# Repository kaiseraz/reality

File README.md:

# Reality: the AI workspace that morphs to the task

**Reality is an open-source AI workspace that turns one sentence into a checked result: a team of AI bots, each with its own Linux computer, builds the work, and independent code verifies every number before it is shown.**

**Built during the Meta Global AI Developer Hackathon (November 2026) on Meta's Muse Spark.** Licensed under Apache 2.0.

You bring only the task. Reality brings the rest: it **acquires the capabilities** the task needs at runtime (a statistics library, a SQL engine, a chemistry toolkit, a CAD kernel), **shapes its workspace** around the work (data, lab, 3D CAD, a bot's live computer), and puts a **team of bots** on it, each with its own Linux computer. What makes it different: **every result is checked by code, independently**. No bot, not even the lead, can declare its own work done.

Built for the Meta Global AI Developer Hackathon, on Meta's Muse Spark.

- Submission text: [docs/submission.md](docs/submission.md)
- Plan and architecture: [docs/execution-plan.md](docs/execution-plan.md) · Decisions: [docs/adr/](docs/adr/)
- Evaluation: [docs/eval/report.md](docs/eval/report.md)

## What it does

**One lead, a team it hires.** Everyone starts with one bot, the lead "Reality". Ask it something small and it answers. Give it a real job and it proposes a team on a card: specialists with a mission, a deliverable, a budget, the web domains and setup their computers need, and how code will check the job. You hire the team once. Each specialist then works under a **contract**: it hands in its work, and code decides whether it is met (a command on its computer exits 0, a file exists with the right content, a Reality task passes verification, or you accept it). Late or unproven work fails. Released bots rest with their **record** of met and failed contracts, and the lead hires proven ones again. Bots save scripts that worked as **team skills** for others to reuse.

**Every bot has its own computer.** A persistent Linux machine per bot (the open-source [AIO Sandbox](https://github.com/agent-infra/sandbox), Apache 2.0) with a browser, a terminal and a home folder that survives restarts. Bots run commands, write files and browse; you watch all computers live as tiles on the right and click one to watch it large or take control. The computers sit on a Docker network **without internet**; Reality's gateway lets each one reach only the domains you allowed, only public addresses on ports 80/443, and logs every decision. Blocked domains turn into Allow/Deny cards.

**A real folder on your computer.** The bots in a chat share one project folder inside the sandbox, and Reality copies what they make to a folder of yours (by default under Reality in your documents; choose another in the Files tab). No bot computer ever has your folder mounted. A file you changed is not overwritten, the new version lands beside it, and nothing there is deleted. On a server, set `PROJECT_FOLDERS=off`.

**More than a computer.** When a picture says it better than words, a bot draws it with `show_visual`: a diagram, a plan or a small interactive page opens beside the chat and updates in versions. It runs in a closed frame without access to Reality's data or the network, and is marked as drawn, not checked.

**It acquires what it lacks.** When a task needs something the sandbox does not have, Reality finds a candidate (a PyPI wheel, or an MCP server from PyPI, npm or the MCP registry), inspects it without running it (files, licence, OSV advisories), asks you once, installs it into an isolated layer, runs a requirement test, then uses and reuses it. Shown live: statsmodels (seasonality), DuckDB via MCP (SQL), RDKit (molecules), OpenCascade (CAD).

**Lab and engineering.** Simulations for thin films, ring resonators, tolerance stacks, quantum circuits, molecules and crystals, each re-checked by an independent method. Ask for a jet engine and Reality acquires a CAD kernel and builds a **turbofan of about 2,000 named solids**, exports **STEP** for any CAD program and shows it in 3D: orbit, cut it open, hide groups, search the parts list. An independent check recounts the parts and recomputes volumes from the meshes. No Fusion, no Python on your machine.

**Design you can watch.** The lab also designs **circuit boards** (placement, a two-layer router with vias and 45° tracks, KiCad 8 board files, Gerber and drill files, part models) and **rockets and assemblies by hierarchy**, each re-checked by an independent method (the board by recomputing clearances and connectivity from the file itself). A bot's result then **opens in the real program on its own desktop**: a board in KiCad first as placed with the ratsnest, then routed, then in KiCad's 3D viewer with the part models; a jet engine in FreeCAD, about 1,900 parts built one at a time in under a minute, coloured by group, shell last and see-through. The web view shows the same boards in physically based 3D, with a build you can replay.

**Bots that operate the programs themselves.** A bot looks at its screen (a picture, plus the text on it read with OCR and its exact position) and uses mouse and keyboard, one action at a time: Muse Spark has opened KiCad's Inspect menu, run the Design Rules Checker, read the result, closed it and saved the board with its own keystrokes. Someone who changes a board by hand (the bot, or you after taking over its desktop) asks for `recheck_board`: the file as KiCad saved it goes through the same independent check, including whether any pad moved to another net.

**Data analysis with proof.** Reality plans, you approve, it runs in a locked-down sandbox, and every number is re-computed independently before it is shown as verified. Numbers a bot writes that no tool produced are flagged in the chat. Evaluation: 14 tasks (6 synthetic with known truth, 8 on NOAA Mauna Loa CO₂ and UCI Bike Sharing): **14/14 correct, 0 policy violations**; a fixed-tool baseline gets 7/14.

**Missions overnight.** Give a team a goal, criteria and a budget; it works until done. The verdict comes from code over fully verified evidence, with a report page.

**And:** research with citations checked against the source (OpenAlex, your notes), versioned pages, routines on a schedule, projects with dependencies and budgets, accounts.

**The interface.** A dark, calm workspace: the sidebar folds with Ctrl+B, the chat in the middle, the bots' computers on the right. Each bot is a [blobatar](https://blobatar.dev/) made from its name, so the same name is the same creature everywhere, and its face shows what it is doing (thinking, searching, working, waiting for you, done). The lead wears the interface's own white; a bot that joins a chat splits off it at the top of that chat, the way the two dots in the logo pull apart.

## Meta Muse Spark

Reality talks to Muse Spark through Meta's Anthropic-compatible Model API. It drives the **bots' conversations and tool use**, the **planner** (structured output via a forced tool call) and **research answers**. `PLANNER=auto` picks Meta whenever `META_MODEL_API_KEY` is set, then Claude, then built-in rules. Without any key, Reality still runs fully with deterministic planners.

Check a key in seconds:

```bash
npm run check:model
```

It verifies that the model answers, calls a tool and uses its result, gives structured output, and accepts all of Reality's bot tools, and says what to fix when a step fails. The bot model tolerates small endpoint differences (string tool arguments, odd stop reasons) and retries passing failures.

## Trust model

- **Verification by code.** Results, contracts and missions are judged by independent checks; a bot's own claim counts for nothing.
- **Sandboxes.** Analysis code runs in containers without network, read-only, non-root. Capabilities are mounted read-only after inspection and your approval.
- **Bot computers.** Isolated network, allowlisted egress through a gateway, no host mounts, resource limits, idle shutdown, a full log. Their screens reach your browser only through Reality, so the computer's key never does.
- **You decide.** Installations, plans with custom code, hiring a team and web access are approvals; a deterministic policy auto-approves only fully machine-checked plans that use reviewed analyses.
- **Tool servers.** Every server a bot gets runs in a sandbox with no network, unless you approved domains for it; then the gateway is its only way out and every other host is refused and named. A hosted server is reached over https only, and its card says who receives what a bot sends.
- **Skills from GitHub, when you ask.** Written methods a bot can get, pinned to a commit, read as text, checked for licence and hidden instructions, and usable once you approved what they say. They bring no rights: their scripts run only on the bot's own computer.
- **Secrets.** Reality's own keys stay in the server and never enter sandboxes or computers. A key you type on a tool server's approval card is stored encrypted, goes only to that server, works only for your bots, and is cut out of whatever comes back. No API returns it and bots never see it.

## Quick start

On Windows, double-click `Start.bat`: it checks Node and Docker, starts Docker Desktop if needed, installs and builds what is missing on the first run (the bot computers are a one-time download of about 9 GB), starts Reality and opens http://localhost:5173.

Or by hand:

```bash
npm install
npm run setup   # Postgres + sandbox images (Docker must be running)
npm run dev     # API on :8787, UI on http://localhost:5173
```

As a desktop app instead of a browser tab: `npm run desktop` opens Reality in its own
window, starts the server if it is not running, and asks for a chat's project folder
in the system's own file explorer, with real paths.

Copy `.env.example` to `.env` and set `META_MODEL_API_KEY` (and optionally `META_MODEL`). The bots' computers need their image once (about 9 GB):

```bash
docker pull ghcr.io/agent-infra/sandbox:1.11.0
```

Results open in KiCad 8 and FreeCAD 0.21 on the bot desktops. `Start.bat` builds that image once by itself (about 2.5 GB on top), since `.env.example` sets `COMPUTER_IMAGE=reality-computer:dev`; by hand it is:

```bash
docker build -t reality-computer:dev sandbox/computer
```

`npm run eval:desktop` and `npm run eval:desktop-cad` run a board and a turbofan through a real bot desktop and take pictures of the screen. `npm run eval:desktop-drive` has the configured model operate KiCad itself (real model calls, a little credit).

On first visit, create your account (the first one is the administrator). For a single-user setup without login, set `AUTH=off`.

## Layout

```
apps/server        Trusted core: API, orchestrator (LangGraph), planners, sandbox runner, capability
                   engine, verifier, lab and CAD, chat engine, team and contracts, bot computers
apps/server/eval   Evaluation suite, Meta probe, lab and CAD smoke tests
apps/web           React SPA: chat, workbench, figures (three.js), lab and CAD views, studio
packages/schemas   Zod contracts shared by server and web
packages/workspace Component registry, patch engine, templates
samples/           Datasets with known ground truth; samples/real: real public data
sandbox/python     Base image for untrusted analysis code
docs/              Execution plan, ADRs, evaluation report, submission
```

## Commands

```bash
npm run check          # typecheck + lint + format check + tests (needs Docker + Postgres)
npm run check:model    # is the configured model (Muse Spark or Claude) ready for Reality?
npm run eval           # evaluation suite → docs/eval/report.md (needs network)
npm run dev:server     # http://127.0.0.1:8787/api/health
npm run dev:web        # http://localhost:5173
npm run desktop        # Reality as a desktop app (Electron), with the system's folder explorer
npm run sandbox:build  # sandbox image only
```

Opt-in tests: `RUN_NETWORK_TESTS=1` (real capability acquisition, CAD kernel), `RUN_COMPUTER_TESTS=1` (a real bot computer behind the gateway). Tests use their own databases; your data is untouched.

## API (selection)

| Method           | Path                                                                   | Purpose                                                    |
| ---------------- | ---------------------------------------------------------------------- | ---------------------------------------------------------- |
| POST / GET       | `/api/tasks`, `/api/tasks/:id`, `/api/tasks/:id/approval`              | Tasks, their state and approval gates                      |
| GET              | `/api/tasks/:id/events`                                                | Live events (SSE)                                          |
| GET              | `/api/capabilities`                                                    | Capability registry with lifecycle and tests               |
| GET / POST       | `/api/bots`, `/api/bots/:id/chat`                                      | Bots (the lead is created on first use) and their chat     |
| GET / POST       | `/api/chats`, `/api/chats/:id/messages`, `/api/chats/:id/answers/:mid` | Chats; answers to questions, access, team and review cards |
| GET / POST       | `/api/missions`, `/api/missions/:id/stop`                              | Missions with goal, criteria, budget and verdict           |
| GET / POST       | `/api/bots/:id/computer`, `/start`, `/stop`, `/access`                 | A bot's computer: status, files, log, allowed domains      |
| GET              | `/api/computers`, `/api/bots/:id/computer/thumb`                       | Which computers are on; a screen picture for the overview  |
| GET              | `/api/bots/:id/computer/screen/*`                                      | The live screen (noVNC and its WebSocket, proxied)         |
| GET              | `/api/files/:id`                                                       | Binary results (STEP, STL)                                 |
| GET / POST / PUT | `/api/pages`, `/api/routines`, `/api/projects`, `/api/knowledge`       | Pages, routines, projects, knowledge                       |
| GET / POST       | `/api/auth/me`, `/api/auth/setup`, `/login`, `/logout`, `/users`       | Accounts (when `AUTH=on`)                                  |

## Status and known gaps

- Muse Spark runs live: `npm run check:model` passes 4/4 against the real endpoint, and bot teams have planned, hired specialists and completed code-checked contracts on it. The 14/14 evaluation was measured with the rule-based planner; a Muse Spark run of that set is still to come.
- Results on the bot desktop are tested on a real computer: board in KiCad (placed, routed, 3D), turbofan in FreeCAD (part by part, under a minute for ~1,900 parts), and Muse Spark operating KiCad (DRC from the menu, save, re-check). On a desktop without a graphics card several parts can land in one repaint late in the build. Screen text comes from OCR: small or unusual labels can be misread, then the bot aims by the picture, which is less exact. The re-check after a hand edit does not judge copper zones and arcs: it says so and the board does not pass. Custom footprints get a generic body with pins, not the real shape of the part.
- Bot computers relax seccomp for the browser (as the AIO Sandbox documents) and give the bot `sudo` inside; isolation rests on the network, no host mounts and limits.
- Not yet: gVisor in a real run, password reset and SSO.

## License and credits

Reality's own code is Apache License 2.0: see [LICENSE](LICENSE) and [NOTICE](NOTICE).

It stands on open source and public data. What it uses and under which licenses:

| Component                                                                                                                                                                                                | Used for                                                              | License                                                                                   |
| -------------------------------------------------------------------------------------------------------------------------------------------------------------------------------------------------------- | --------------------------------------------------------------------- | ----------------------------------------------------------------------------------------- |
| [AIO Sandbox](https://github.com/agent-infra/sandbox) — `ghcr.io/agent-infra/sandbox`                                                                                                                    | the base image for a bot's own computer                               | Apache-2.0                                                                                |
| [Blobatar](https://blobatar.dev/) — `@blobatar/react`                                                                                                                                                    | the bots' animated figures                                            | MIT                                                                                       |
| [LangGraph.js](https://github.com/langchain-ai/langgraphjs) (`@langchain/langgraph`)                                                                                                                     | the orchestrator's graphs, checkpoints and interrupts                 | MIT                                                                                       |
| [Model Context Protocol TypeScript SDK](https://github.com/modelcontextprotocol/typescript-sdk)                                                                                                          | tool protocol for acquired capability servers                         | MIT                                                                                       |
| Fastify, Zod, React, Vite, three.js, dockview, xterm                                                                                                                                                     | server framework, contracts, UI and its parts                         | MIT (each component's own)                                                                |
| [statsmodels](https://www.statsmodels.org/), [RDKit](https://www.rdkit.org/), [DuckDB](https://duckdb.org/), [OpenCascade](https://github.com/Open-Cascade-SAS/OCCT) via `cadquery-ocp`                  | capabilities a bot can acquire for statistics, molecules, SQL and CAD | BSD-3 (statsmodels, RDKit), MIT (DuckDB), LGPL-2.1 with the Open CASCADE exception (OCCT) |
| [OpenAlex](https://openalex.org/)                                                                                                                                                                        | the public API behind research steps                                  | public API                                                                                |
| [NOAA GML Mauna Loa CO₂ monthly means](https://gml.noaa.gov/ccgg/trends/data.html) (Dr. Xin Lan, NOAA/GML, and Dr. Ralph Keeling, Scripps Institution of Oceanography)                                   | real public data in `samples/real/co2_mm_mlo.csv`                     | public domain (U.S. Government work; NOAA asks for citation)                              |
| [UCI Bike Sharing Dataset](https://doi.org/10.24432/C5W894), Fanaee-T, H. & Gama, J. (2013), _Event labeling combining ensemble detectors and background knowledge_, Progress in Artificial Intelligence | real public data in `samples/real/bike_day.csv`                       | CC BY 4.0                                                                                 |

> This folder is inside OneDrive. If syncing `node_modules` causes slowness or file locks, move the repo outside OneDrive or exclude `node_modules` from sync.

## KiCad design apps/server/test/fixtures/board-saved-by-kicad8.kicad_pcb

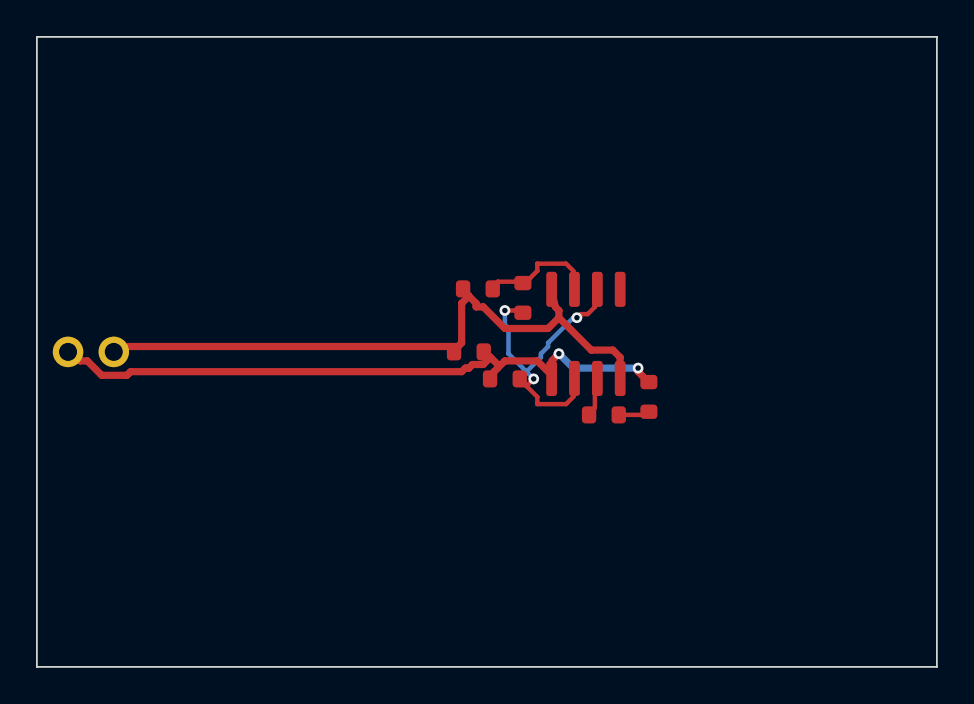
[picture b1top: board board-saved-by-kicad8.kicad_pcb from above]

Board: 2 copper layers, 50.0 x 35.0 mm, 8 parts (0 on the bottom side), 6 nets.

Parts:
C1: 10u; C0603
C2: 100n; C0603
D1: red; LED0603
J1: power; HEADER1x2
R1: 10k; R0603
R2: 47k; R0603
R3: 470; R0603
U1: NE555; SOIC8

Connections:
DIS: R1.2, R2.1, U1.7
GND: C1.2, C2.2, D1.2, J1.2, U1.1
LED: D1.1, R3.2
OUT: R3.1, U1.3
TRIG: C1.1, R2.2, U1.2, U1.6
VCC: C2.1, J1.1, R1.1, U1.4, U1.8
